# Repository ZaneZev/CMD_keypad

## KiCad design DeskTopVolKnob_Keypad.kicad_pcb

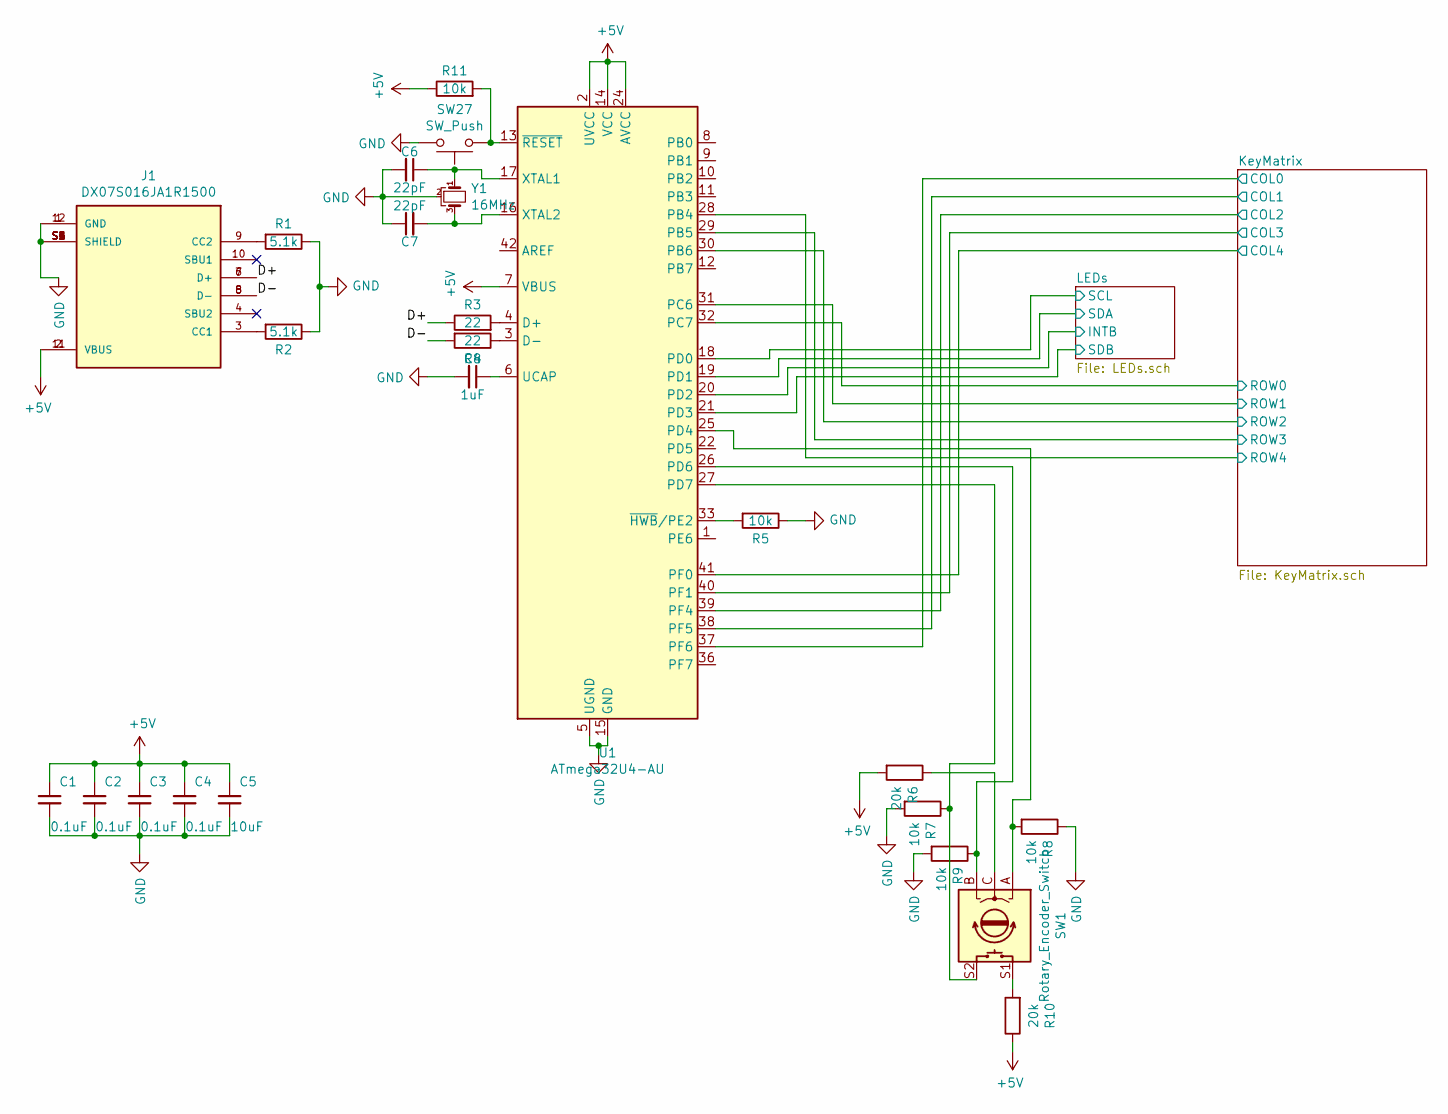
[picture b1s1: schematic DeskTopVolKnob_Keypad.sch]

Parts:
C1, C2, C3, C4: 0.1uF; C_0402_1005Metric
C5: 10uF; C_0805_2012Metric
C6, C7: 22pF; C_0603_1608Metric
C8: 1uF; C_0402_1005Metric
J1: DX07S016JA1R1500; JAE_DX07S016JA1R1500; PARTREV 1
R1, R2: 5.1k; R_0603_1608Metric
R3, R4: 22; R_0603_1608Metric
R5, R7, R8, R9, R11: 10k; R_0603_1608Metric
R6, R10: 20k; R_0603_1608Metric
SW1: Rotary_Encoder_Switch; RotaryEncoder_Alps_EC12E-Switch_Vertical_H20mm
SW27: SW_Push; SW_SPST_B3S-1000
U1: ATmega32U4-AU; TQFP-44_10x10mm_P0.8mm
Y1: 16MHz; Crystal_SMD_2520-4Pin_2.5x2.0mm

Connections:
+5V: C1.1, C2.1, C3.1, C4.1, C5.1, J1.2 (VBUS), J1.11 (VBUS), R6.2, R10.1, R11.1, U1.2 (UVCC), U1.7 (VBUS), U1.14 (VCC), U1.24 (AVCC), U1.34 (VCC), U1.44 (AVCC); also elsewhere on the board
/D+: J1.6 (D+), J1.7 (D+), R3.1
/D-: J1.5 (D-), J1.8 (D-), R4.2
/KeyMatrix/COL0: U1.37 (PF6); also elsewhere on the board
/KeyMatrix/COL1: U1.38 (PF5); also elsewhere on the board
/KeyMatrix/COL2: U1.39 (PF4); also elsewhere on the board
/KeyMatrix/COL3: U1.40 (PF1); also elsewhere on the board
/KeyMatrix/COL4: U1.41 (PF0); also elsewhere on the board
/KeyMatrix/ROW0: U1.32 (PC7); also elsewhere on the board
/KeyMatrix/ROW1: U1.31 (PC6); also elsewhere on the board
/KeyMatrix/ROW2: U1.30 (PB6); also elsewhere on the board
/KeyMatrix/ROW3: U1.29 (PB5); also elsewhere on the board
/KeyMatrix/ROW4: U1.28 (PB4); also elsewhere on the board
/LEDs/INTB: U1.20 (PD2); also elsewhere on the board
/LEDs/SCL: U1.18 (PD0); also elsewhere on the board
/LEDs/SDA: U1.19 (PD1); also elsewhere on the board
/LEDs/SDB: U1.21 (PD3); also elsewhere on the board
GND: C1.2, C2.2, C3.2, C4.2, C5.2, C6.2, C7.1, C8.2, J1.1 (GND), J1.12 (GND), J1.S1 (SHIELD), J1.S2 (SHIELD), J1.S3 (SHIELD), J1.S4 (SHIELD), J1.S5 (SHIELD), J1.S6 (SHIELD), R1.1, R2.1, R5.1, R7.2, R8.1, R9.2, SW27.2, U1.5 (UGND), U1.15 (GND), U1.23 (GND), U1.35 (GND), U1.43 (GND), Y1.2; also elsewhere on the board
unnamed: C6.1, U1.17 (XTAL1), Y1.1
unnamed: C7.2, U1.16 (XTAL2), Y1.3
unnamed: C8.1, U1.6 (UCAP)
unnamed: J1.3 (CC1), R2.2
unnamed: J1.9 (CC2), R1.2
unnamed: R3.2, U1.4 (D+)
unnamed: R4.1, U1.3 (D-)
unnamed: R5.2, U1.33 (~HWB~/PE2)
unnamed: R6.1, SW1.C
unnamed: R7.1, SW1.S2, U1.27 (PD7)
unnamed: R8.2, SW1.A, U1.25 (PD4)
unnamed: R9.1, SW1.B, U1.26 (PD6)
unnamed: R10.2, SW1.S1
unnamed: R11.2, SW27.1, U1.13 (~RESET)

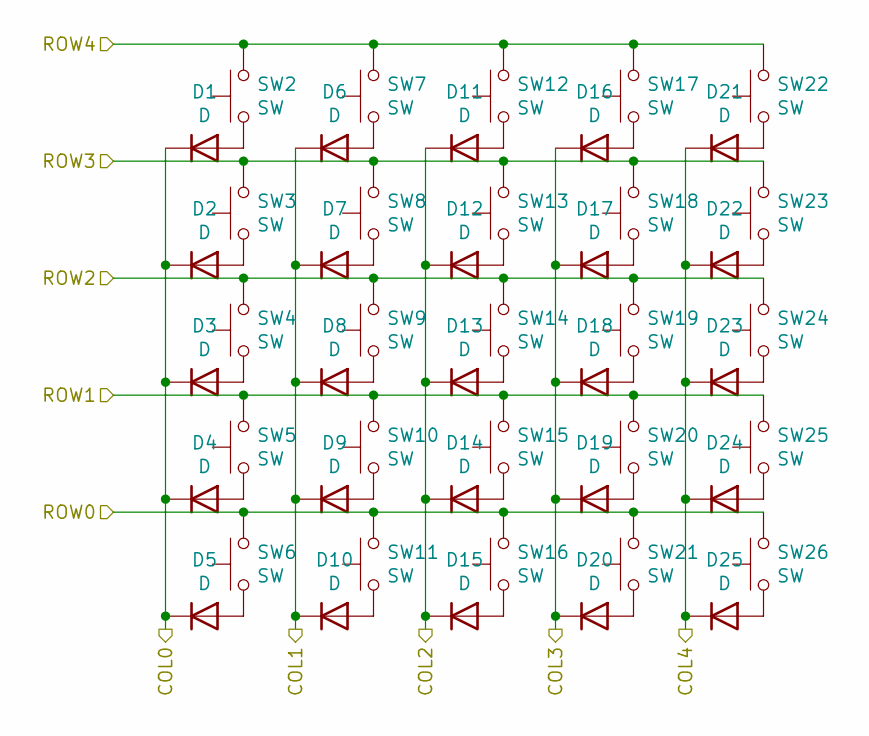
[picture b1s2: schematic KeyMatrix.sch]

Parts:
D1, D2, D3, D4, D5, D6, D7, D8, D9, D10, D11, D12, D13, D14, D15, D16, D17, D18, D19, D20, D21, D22, D23, D24, D25: D; D_SOD-523
SW2, SW3, SW4, SW5, SW6, SW7, SW8, SW9, SW10, SW11, SW12, SW13, SW14, SW15, SW16, SW17, SW18, SW19, SW20, SW21, SW22, SW23, SW24, SW25, SW26: SW; SW_Cherry_MX_1.00u_PCB

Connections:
/KeyMatrix/COL0: D1.1 (K), D2.1 (K), D3.1 (K), D4.1 (K), D5.1 (K); also elsewhere on the board
/KeyMatrix/COL1: D6.1 (K), D7.1 (K), D8.1 (K), D9.1 (K), D10.1 (K); also elsewhere on the board
/KeyMatrix/COL2: D11.1 (K), D12.1 (K), D13.1 (K), D14.1 (K), D15.1 (K); also elsewhere on the board
/KeyMatrix/COL3: D16.1 (K), D17.1 (K), D18.1 (K), D19.1 (K), D20.1 (K); also elsewhere on the board
/KeyMatrix/COL4: D21.1 (K), D22.1 (K), D23.1 (K), D24.1 (K), D25.1 (K); also elsewhere on the board
/KeyMatrix/ROW0: SW6.2, SW11.2, SW16.2, SW21.2, SW26.2; also elsewhere on the board
/KeyMatrix/ROW1: SW5.2, SW10.2, SW15.2, SW20.2, SW25.2; also elsewhere on the board
/KeyMatrix/ROW2: SW4.2, SW9.2, SW14.2, SW19.2, SW24.2; also elsewhere on the board
/KeyMatrix/ROW3: SW3.2, SW8.2, SW13.2, SW18.2, SW23.2; also elsewhere on the board
/KeyMatrix/ROW4: SW2.2, SW7.2, SW12.2, SW17.2, SW22.2; also elsewhere on the board
unnamed: D1.2 (A), SW2.1
unnamed: D2.2 (A), SW3.1
unnamed: D3.2 (A), SW4.1
unnamed: D4.2 (A), SW5.1
unnamed: D5.2 (A), SW6.1
unnamed: D6.2 (A), SW7.1
unnamed: D7.2 (A), SW8.1
unnamed: D8.2 (A), SW9.1
unnamed: D9.2 (A), SW10.1
unnamed: D10.2 (A), SW11.1
unnamed: D11.2 (A), SW12.1
unnamed: D12.2 (A), SW13.1
unnamed: D13.2 (A), SW14.1
unnamed: D14.2 (A), SW15.1
unnamed: D15.2 (A), SW16.1
unnamed: D16.2 (A), SW17.1
unnamed: D17.2 (A), SW18.1
unnamed: D18.2 (A), SW19.1
unnamed: D19.2 (A), SW20.1
unnamed: D20.2 (A), SW21.1
unnamed: D21.2 (A), SW22.1
unnamed: D22.2 (A), SW23.1
unnamed: D23.2 (A), SW24.1
unnamed: D24.2 (A), SW25.1
unnamed: D25.2 (A), SW26.1

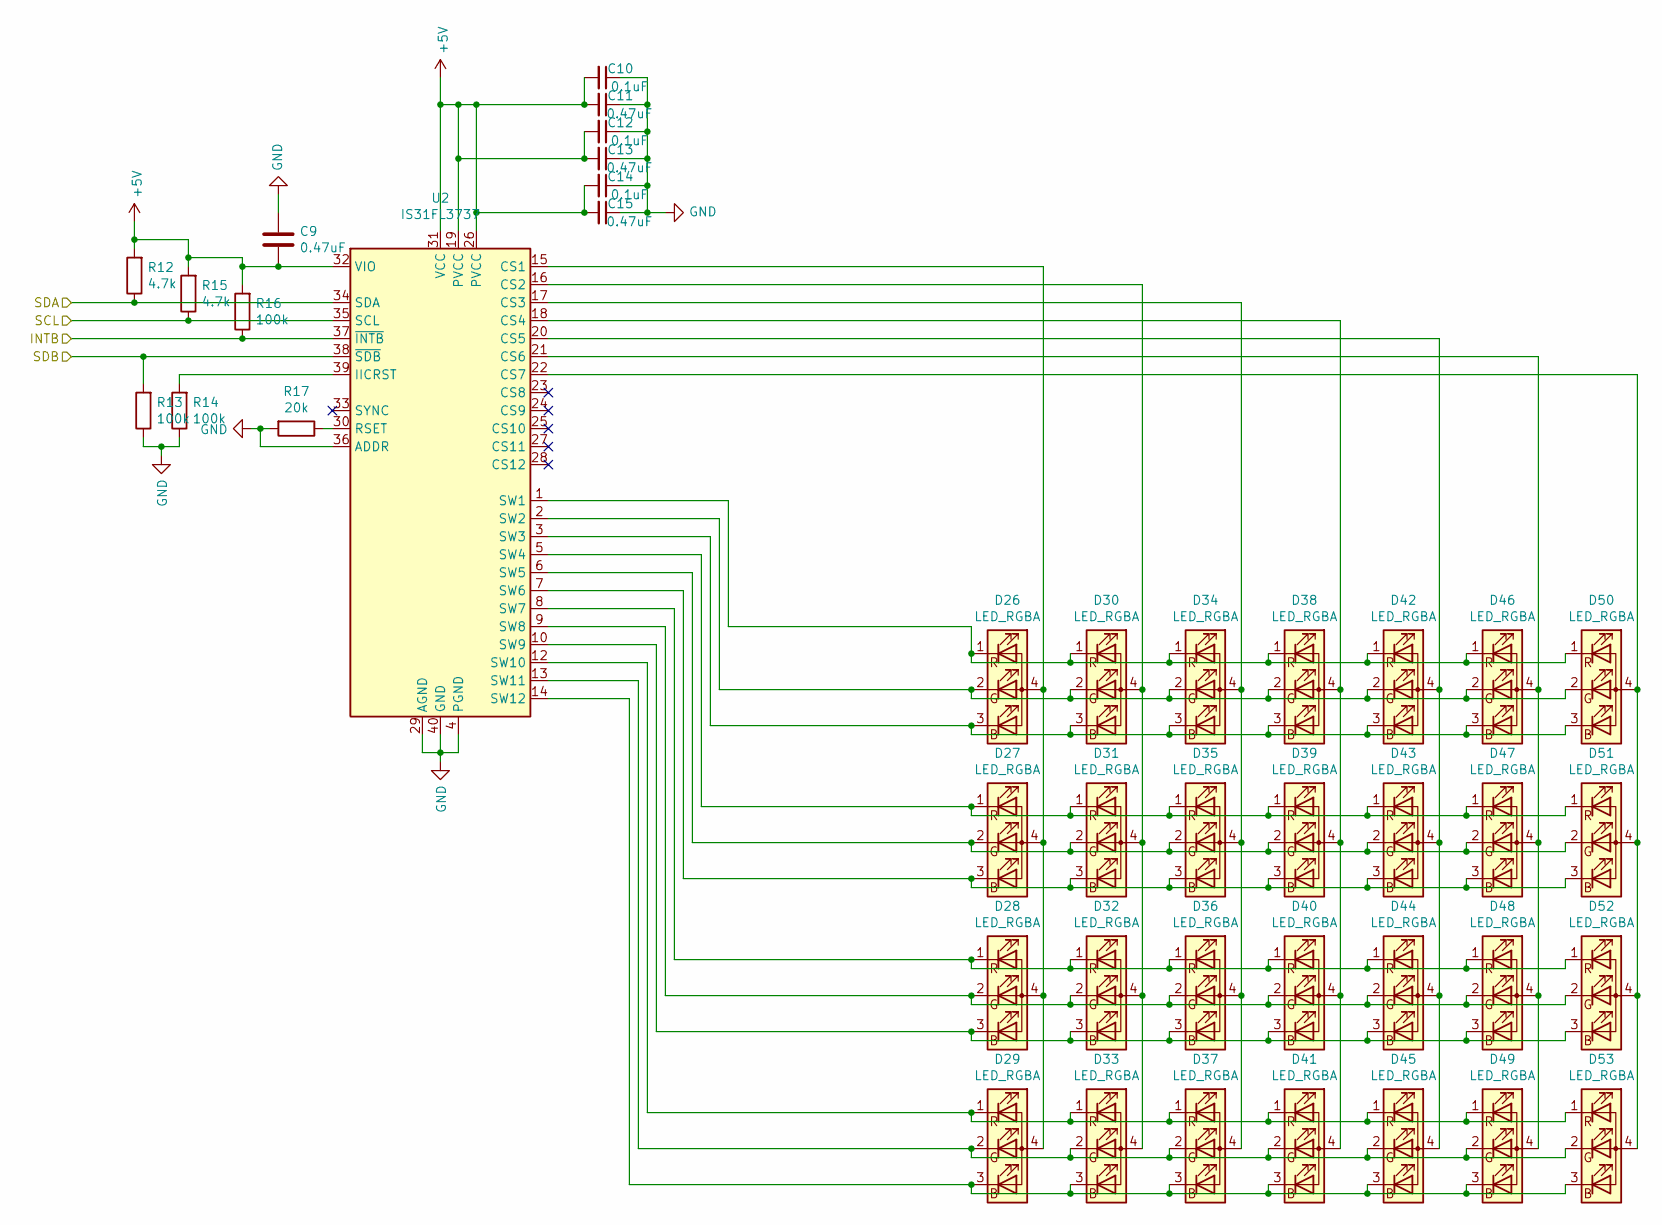
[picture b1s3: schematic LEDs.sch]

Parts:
C9, C11, C13, C15: 0.47uF; C_0603_1608Metric
C10, C12, C14: 0.1uF; C_0402_1005Metric
D26, D27, D28, D29, D30, D31, D32, D33, D34, D35, D36, D37, D38, D39, D40, D41, D42, D43, D44, D45, D46, D47, D48, D49, D50, D51, D52, D53: LED_RGBA; LED_Cree-PLCC4_2x2mm_CW
R12, R15: 4.7k; R_0603_1608Metric
R13, R14, R16: 100k; R_0603_1608Metric
R17: 20k; R_0603_1608Metric
U2: IS31FL3737; QFN-40-1EP_5x5mm_P0.4mm_EP3.8x3.8mm

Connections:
+5V: C9.2, C10.2, C11.2, C12.2, C13.2, C14.2, C15.2, R12.2, R15.2, R16.2, U2.19 (PVCC), U2.26 (PVCC), U2.31 (VCC), U2.32 (VIO); also elsewhere on the board
/LEDs/INTB: R16.1, U2.37 (~INTB); also elsewhere on the board
/LEDs/SCL: R15.1, U2.35 (SCL); also elsewhere on the board
/LEDs/SDA: R12.1, U2.34 (SDA); also elsewhere on the board
/LEDs/SDB: R13.2, U2.38 (~SDB); also elsewhere on the board
GND: C9.1, C10.1, C11.1, C12.1, C13.1, C14.1, C15.1, R13.1, R14.1, R17.2, U2.4 (PGND), U2.11 (PGND), U2.29 (AGND), U2.36 (ADDR), U2.40 (GND), U2.41 (GND); also elsewhere on the board
unnamed: D26.1 (RK), D30.1 (RK), D34.1 (RK), D38.1 (RK), D42.1 (RK), D46.1 (RK), D50.1 (RK), U2.1 (SW1)
unnamed: D26.2 (GK), D30.2 (GK), D34.2 (GK), D38.2 (GK), D42.2 (GK), D46.2 (GK), D50.2 (GK), U2.2 (SW2)
unnamed: D26.3 (BK), D30.3 (BK), D34.3 (BK), D38.3 (BK), D42.3 (BK), D46.3 (BK), D50.3 (BK), U2.3 (SW3)
unnamed: D26.4 (A), D27.4 (A), D28.4 (A), D29.4 (A), U2.15 (CS1)
unnamed: D27.1 (RK), D31.1 (RK), D35.1 (RK), D39.1 (RK), D43.1 (RK), D47.1 (RK), D51.1 (RK), U2.5 (SW4)
unnamed: D27.2 (GK), D31.2 (GK), D35.2 (GK), D39.2 (GK), D43.2 (GK), D47.2 (GK), D51.2 (GK), U2.6 (SW5)
unnamed: D27.3 (BK), D31.3 (BK), D35.3 (BK), D39.3 (BK), D43.3 (BK), D47.3 (BK), D51.3 (BK), U2.7 (SW6)
unnamed: D28.1 (RK), D32.1 (RK), D36.1 (RK), D40.1 (RK), D44.1 (RK), D48.1 (RK), D52.1 (RK), U2.8 (SW7)
unnamed: D28.2 (GK), D32.2 (GK), D36.2 (GK), D40.2 (GK), D44.2 (GK), D48.2 (GK), D52.2 (GK), U2.9 (SW8)
unnamed: D28.3 (BK), D32.3 (BK), D36.3 (BK), D40.3 (BK), D44.3 (BK), D48.3 (BK), D52.3 (BK), U2.10 (SW9)
unnamed: D29.1 (RK), D33.1 (RK), D37.1 (RK), D41.1 (RK), D45.1 (RK), D49.1 (RK), D53.1 (RK), U2.12 (SW10)
unnamed: D29.2 (GK), D33.2 (GK), D37.2 (GK), D41.2 (GK), D45.2 (GK), D49.2 (GK), D53.2 (GK), U2.13 (SW11)
unnamed: D29.3 (BK), D33.3 (BK), D37.3 (BK), D41.3 (BK), D45.3 (BK), D49.3 (BK), D53.3 (BK), U2.14 (SW12)
unnamed: D30.4 (A), D31.4 (A), D32.4 (A), D33.4 (A), U2.16 (CS2)
unnamed: D34.4 (A), D35.4 (A), D36.4 (A), D37.4 (A), U2.17 (CS3)
unnamed: D38.4 (A), D39.4 (A), D40.4 (A), D41.4 (A), U2.18 (CS4)
unnamed: D42.4 (A), D43.4 (A), D44.4 (A), D45.4 (A), U2.20 (CS5)
unnamed: D46.4 (A), D47.4 (A), D48.4 (A), D49.4 (A), U2.21 (CS6)
unnamed: D50.4 (A), D51.4 (A), D52.4 (A), D53.4 (A), U2.22 (CS7)
unnamed: R14.2, U2.39 (IICRST)
unnamed: R17.1, U2.30 (RSET)

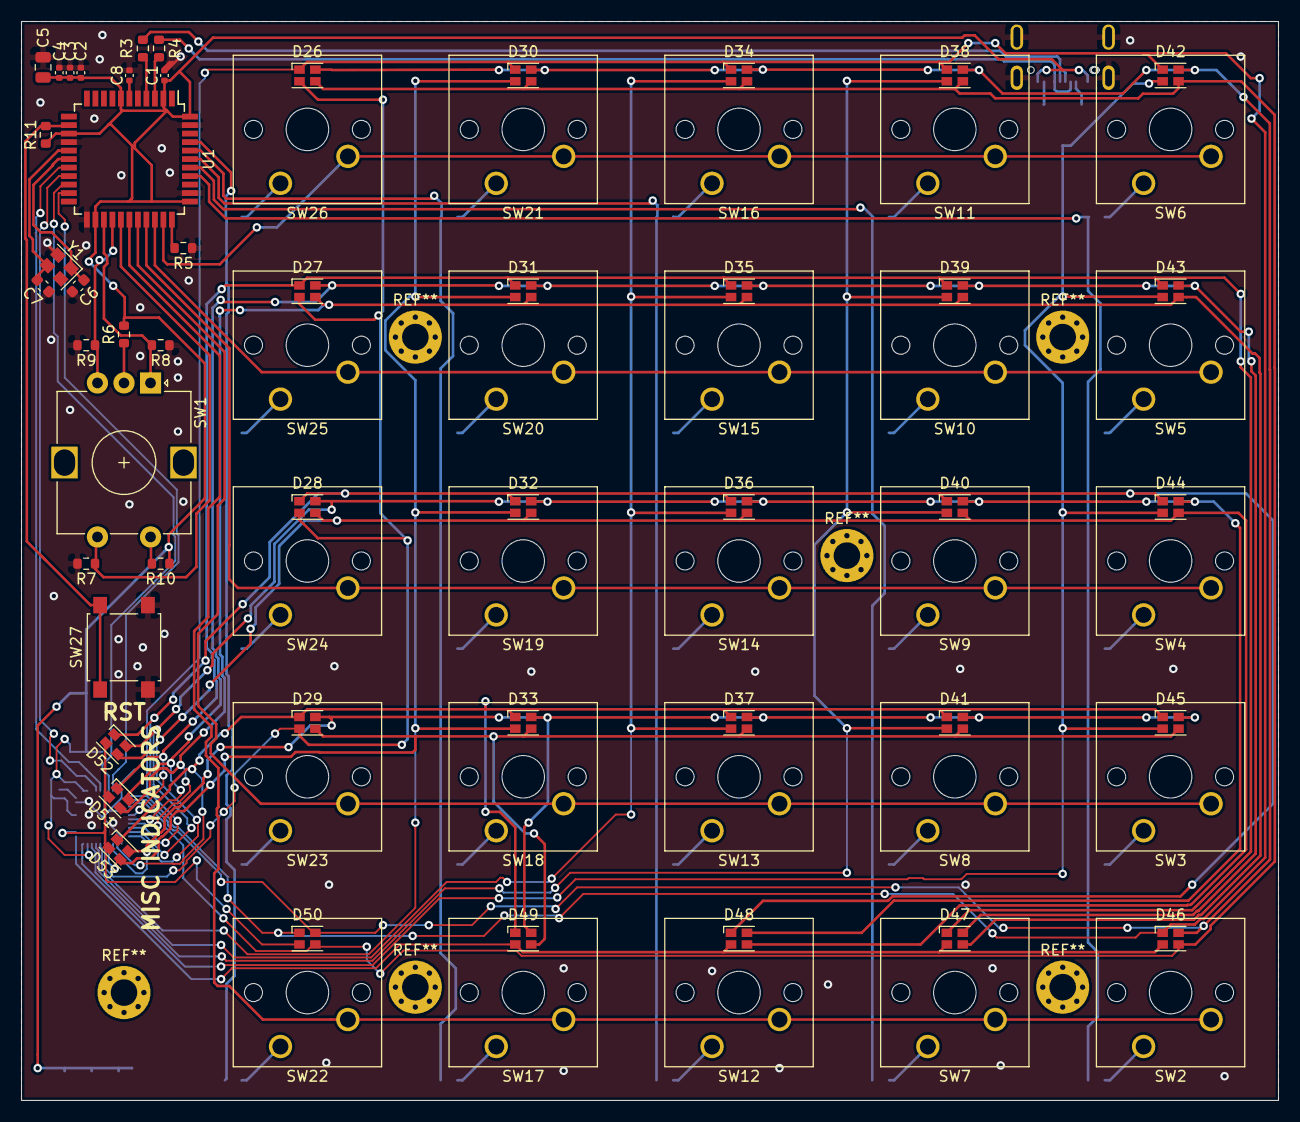
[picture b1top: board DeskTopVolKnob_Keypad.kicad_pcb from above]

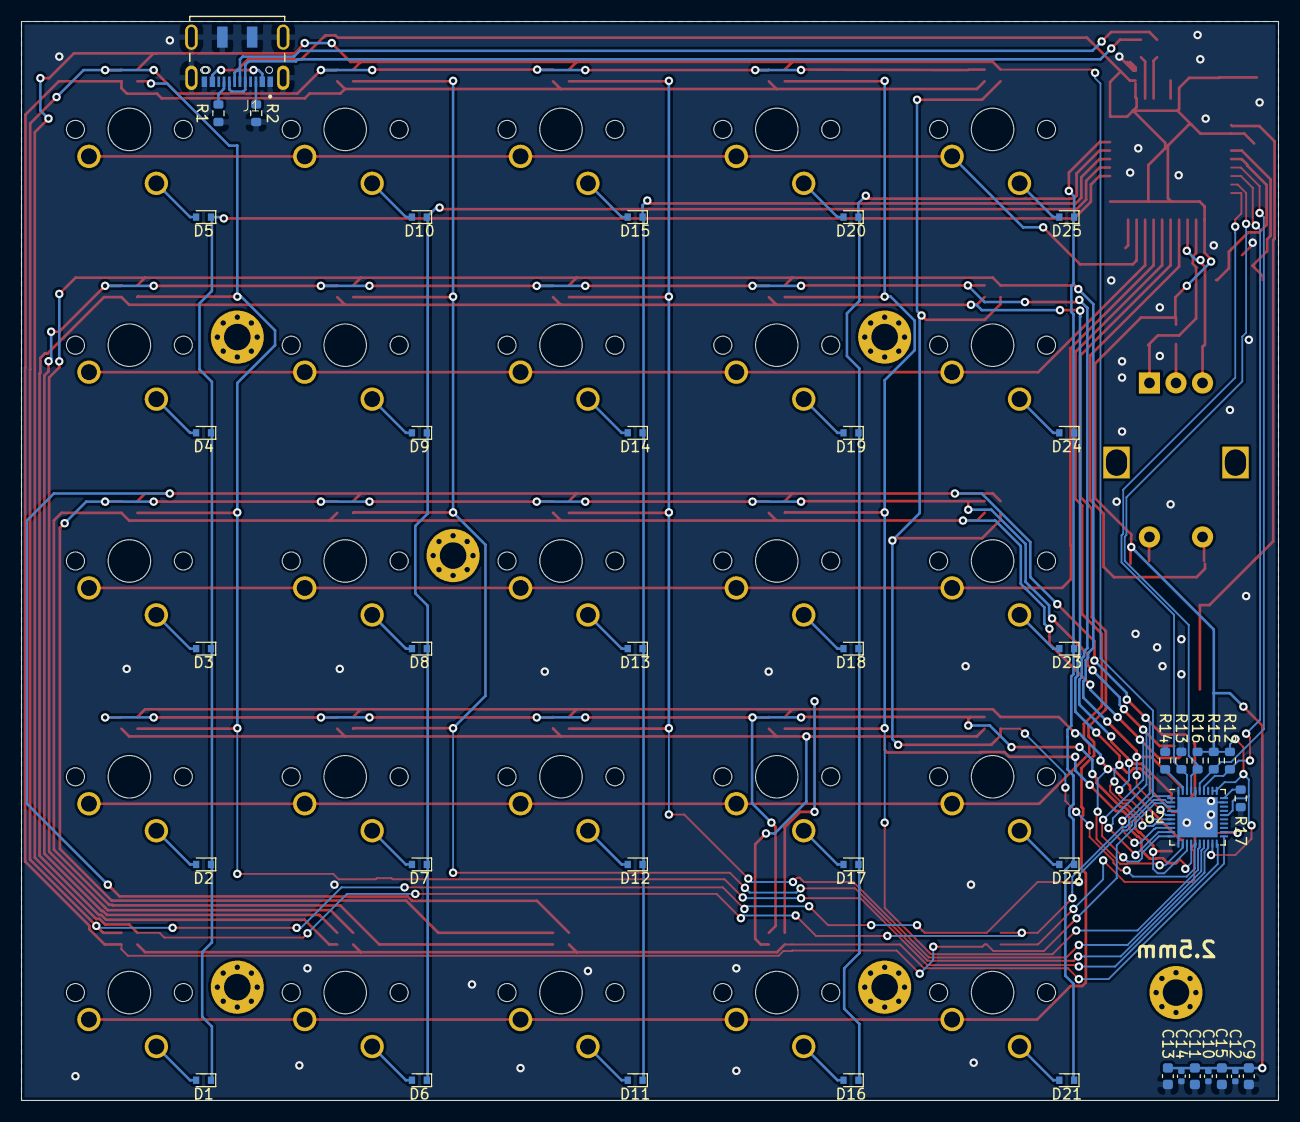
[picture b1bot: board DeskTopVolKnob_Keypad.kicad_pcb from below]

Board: 2 copper layers, 118.3 x 101.5 mm, 116 parts (42 on the bottom side), 78 nets.

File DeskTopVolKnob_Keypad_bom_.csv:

Component,Description,Part,References,Value,Footprint,Quantity Per PCB,Datasheet
1,"Unpolarized capacitor, small symbol",C_Small,C6 C7,22pF,C_0805_2012Metric,2,~
2,"Unpolarized capacitor, small symbol",C_Small,C1 C2 C3 C4,0.1uF,C_0805_2012Metric,4,~
3,"Unpolarized capacitor, small symbol",C_Small,C8,1uF,D_0603_1608Metric,1,~
4,"Unpolarized capacitor, small symbol",C_Small,C5,10uF,C_0805_2012Metric,1,~
5,RGB LED with integrated controller,APA102-2020,D26 D27 D28 D29 D30 D31 D32 D33 D34 D35 D36 D37 D38 D39 D40 D41 D42 D43 D44 D45 D46 D47 D48 D49 D50,APA102-2020,LED-APA102-2020,25,http://www.led-color.com/upload/201604/APA102-2020%20SMD%20LED.pdf
6,Diode,D,D1 D2 D3 D4 D5 D6 D7 D8 D9 D10 D11 D12 D13 D14 D15 D16 D17 D18 D19 D20 D21 D22 D23 D24 D25,D,D_0603_1608Metric,25,~
7,USB 2.0-only Type-C Receptacle connector,USB_C_Receptacle_USB2.0,J1,USB_C_Receptacle_USB2.0,USB_C_Receptacle_Palconn_UTC16-G,1,https://www.usb.org/sites/default/files/documents/usb_type-c.zip
8,Resistor,R,R3 R4,22,R_0805_2012Metric,2,~
9,Resistor,R,R1 R2,5.1k,R_0805_2012Metric,2,~
10,Resistor,R,R5 R7 R8 R9,10k,R_0805_2012Metric,4,~
11,Resistor,R,R6 R10,20k,R_0805_2012Metric,2,~
12,"Rotary encoder, dual channel, incremental quadrate outputs, with switch",Rotary_Encoder_Switch,SW1,Rotary_Encoder_Switch,RotaryEncoder_Alps_EC12E-Switch_Vertical_H20mm,1,~
13,"Push button switch, generic, two pins",SW_Push,SW2 SW3 SW4 SW5 SW6 SW7 SW8 SW9 SW10 SW11 SW12 SW13 SW14 SW15 SW16 SW17 SW18 SW19 SW20 SW21 SW22 SW23 SW24 SW25 SW26,SW,SW_Cherry_MX_1.00u_PCB,25,~
14,"16MHz, 32kB Flash, 2.5kB SRAM, 1kB EEPROM, USB 2.0, TQFP-44",ATmega32U4-AU,U1,ATmega32U4-AU,TQFP-44_10x10mm_P0.8mm,1,http://ww1.microchip.com/downloads/en/DeviceDoc/Atmel-7766-8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
15,"Three pin crystal, GND on pin 2, small symbol",Crystal_GND2_Small,Y1,16MHz,Crystal_HC52-U-3Pin_Vertical,1,~
,,,,,,,
,,,,,,,
,,,,,,,
,,,,,,,
,,,,,,,
,,,,,,,
,,,,,,,
,,,,,,,
,,,,,,,
,,,,,,,
,,,,,,,
,,,,,,,
,,,,,,,
,,,,,,,

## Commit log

2020-12-20 init commit
2020-12-21 new LEDs and crystal cap fixed
2021-01-27 moved to the SK6805-EC15 LEDs , there are still problems
2021-03-18 LEDs redesigned for ili controller
